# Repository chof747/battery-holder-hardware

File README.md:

# battery-holder-hardware
Little PCB with a simple charger for Li-Ion devices

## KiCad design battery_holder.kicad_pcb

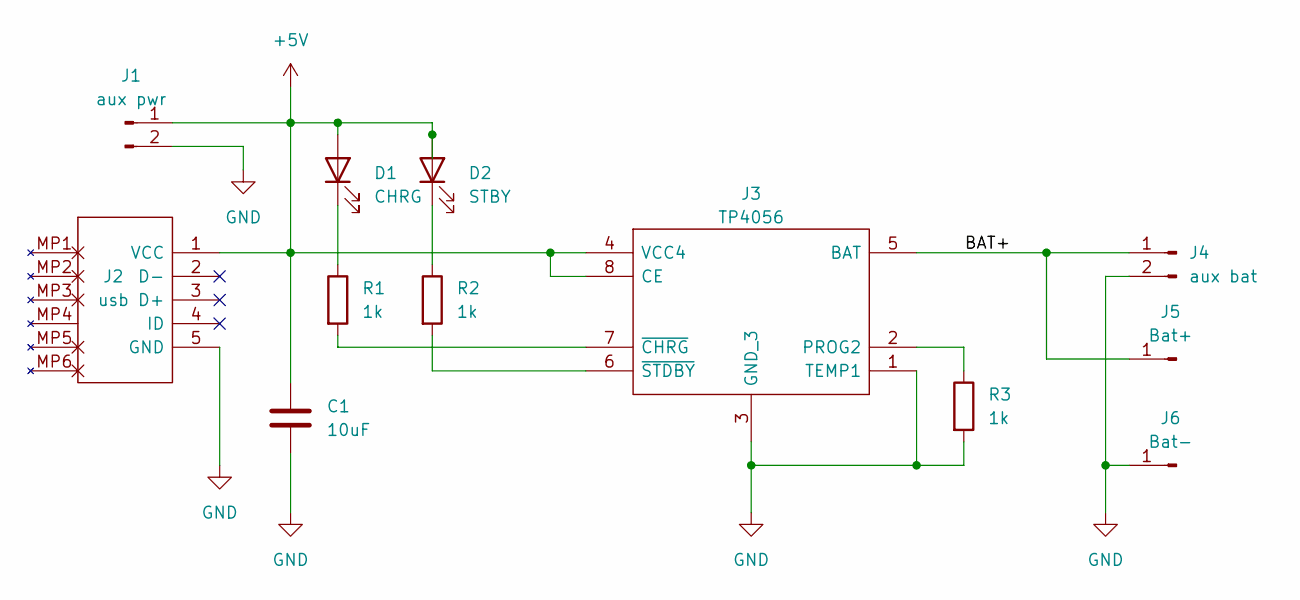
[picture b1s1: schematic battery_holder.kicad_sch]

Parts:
C1: 10uF; C_0603_1608Metric
D1: CHRG; LED_0603_1608Metric
D2: STBY; LED_0603_1608Metric
J1: aux pwr; PinHeader_1x02_P2.54mm_Vertical
J2: usb; 101181920002LF; Manufacturer_Part_Number 10118192-0002LF
J3: TP4056; SOIC127P600X175-9N; Manufacturer_Part_Number TP4056
J4: aux bat; PinHeader_1x02_P2.54mm_Vertical
J5: Bat+; SolderWirePad_1x01_SMD_2x3mm
J6: Bat-; SolderWirePad_1x01_SMD_2x3mm
R1, R2, R3: 1k; R_0603_1608Metric

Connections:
+5V: C1.1, D1.2 (A), D2.2 (A), J1.1, J2.1 (VCC), J3.4 (VCC4), J3.8 (CE)
/BAT+: J3.5 (BAT), J4.1, J5.1
GND: C1.2, J1.2, J2.5 (GND), J3.1 (TEMP1), J3.3 (GND_3), J4.2, J6.1, R3.2
unnamed: D1.1 (K), R1.1
unnamed: D2.1 (K), R2.1
unnamed: J3.2 (PROG2), R3.1
unnamed: J3.6 (~STDBY), R2.2
unnamed: J3.7 (~CHRG), R1.2

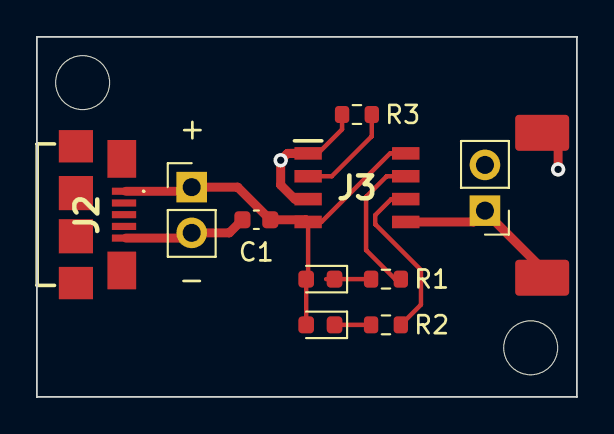
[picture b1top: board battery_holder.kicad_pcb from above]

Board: 2 copper layers, 30.0 x 20.0 mm, 12 parts (0 on the bottom side), 8 nets.

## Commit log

2022-10-31 Initial versiion of battery charging board
2023-04-19 Updates according to newest template
    - added logo
    - changed to new format of .gitignore
2023-04-19 Added +/- signs on input pins
2023-04-27 Updated template for KiCAD 7
